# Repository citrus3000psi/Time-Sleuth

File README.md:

# Time Sleuth

A cheap and easy to build HDMI lag tester.  Through hole components were chosen to aid in assembly.  Resistors and Caps are still surface mount but a larger 0805 package size. 

An altera USB-Blaster is required to program the board. Firmware was created by Chriz2600 and can be found on his Github https://github.com/chriz2600/time-sleuth

For convenience the V1.1 PCB is shared on OSH Park.  Please order in 1.6mm thickness.
https://oshpark.com/shared_projects/Jw3gMtl8

A 3D printed case is also available but not required for the unit to function.  The STL file can be downloaded from here:
https://www.shapeways.com/product/DRHQ8MRWT/time-sleuth-top
https://www.shapeways.com/product/R2SNB5DNT/time-sleuth-bottom

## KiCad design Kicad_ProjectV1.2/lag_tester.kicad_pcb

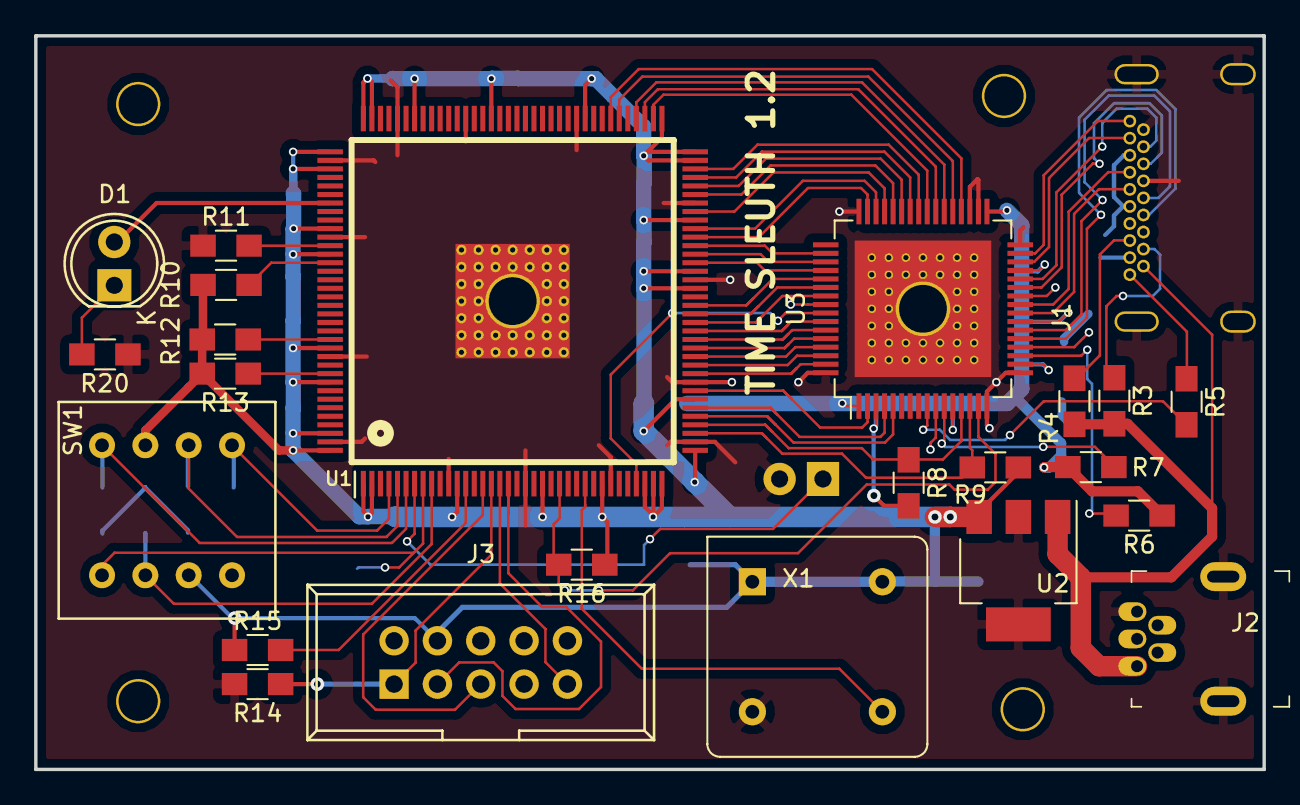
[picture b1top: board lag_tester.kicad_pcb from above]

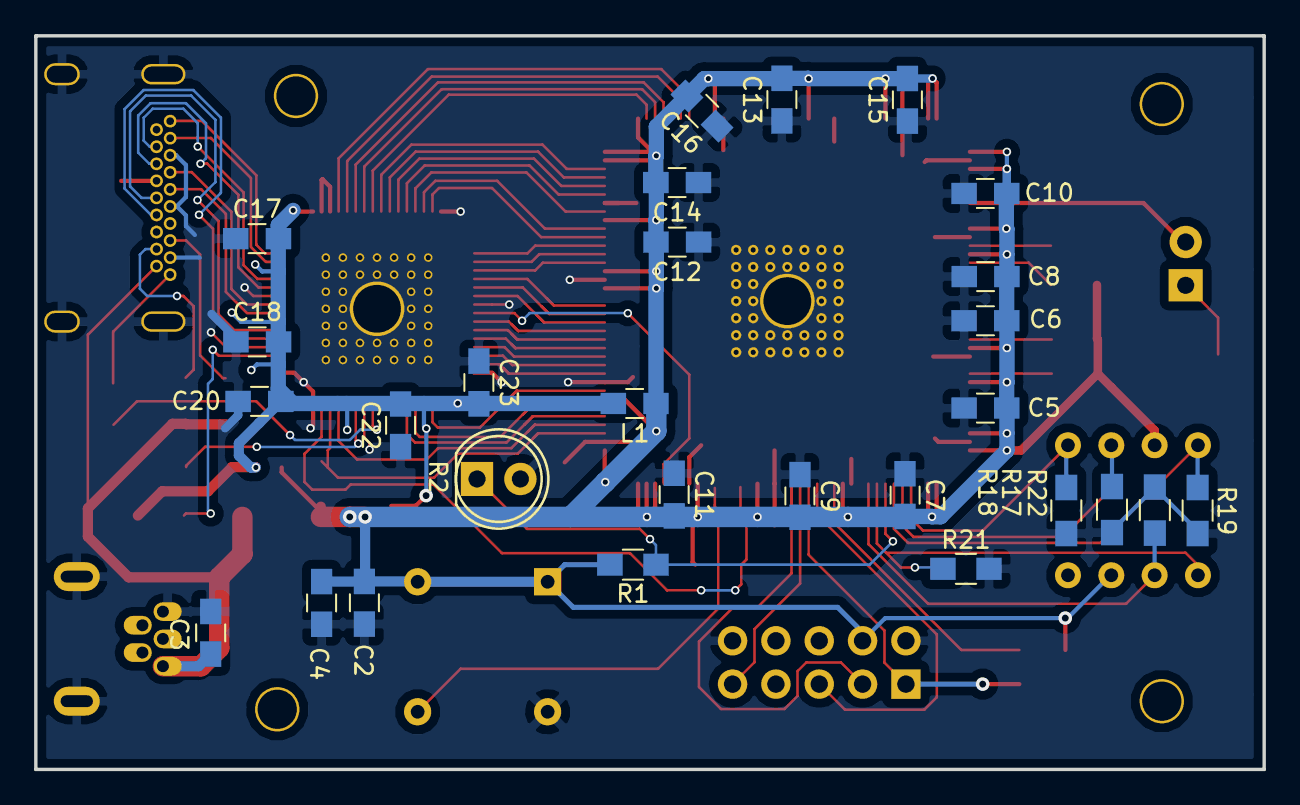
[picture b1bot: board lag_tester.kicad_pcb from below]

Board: 2 copper layers, 72.0 x 43.0 mm, 52 parts (28 on the bottom side), 67 nets.

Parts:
C2, C3, C23: 10u; C_0805_HandSoldering
C4, C5, C6, C7, C8, C9, C10, C11, C12, C13, C14, C15, C16, C17, C18, C20, C22: .1u; C_0805_HandSoldering
D1: LED; LED-5MM
J1: HDMI_A; HDMI_THRU
J2: USB_B_Mini; USB_Mini_B_Female_548190519
J3: AVR-JTAG-10; IDC_Header_Straight_10pins
L1: INDUCTOR; C_0805_HandSoldering
R1: 150; R_0805_HandSoldering
R2: R_PHOTO; LED-5MM
R3, R4, R10, R11, R12, R13, R14, R15, R17, R18, R19, R21, R22: 10K; R_0805_HandSoldering
R5: 1k; R_0805_HandSoldering
R6: 510; R_0805_HandSoldering
R7: 5K; R_0805_HandSoldering
R8, R9, R16: 2.2K; R_0805_HandSoldering
R20: 1K; R_0805_HandSoldering
SW1: SW_Coded; SS-10-23NP-LE
U1: 10M02SCE144I7G; altera144_wcenterpad
U2: TC1264-3.3VDBTR; SOT-223-3Lead_TabPin2
U3: TFP410PAP; TQFP-64_1EP_10x10mm_Pitch0.5mm
X1: CXO_DIP8; Oscillator_DIP-8

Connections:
/27CLK: U1.27, X1.5
/+3.3: C2.2, C4.2, C5.2, C6.2, C7.2, C8.2, C9.2, C10.2, C11.2, C12.2, C13.2, C14.2, C15.2, C16.2, J3.4, L1.1, R1.2, R9.1, R10.1, R12.1, R13.1, R15.1, R16.1, SW1.2, SW1.6, U1.1, U1.2, U1.12, U1.22, U1.29, U1.34, U1.35, U1.36, U1.37, U1.43, U1.56, U1.58, U1.64, U1.71, U1.72, U1.73, U1.82, U1.93, U1.102, U1.107, U1.108, U1.109, U1.111, U1.118, U1.121, U1.132, U1.136, U1.142, U1.144, U2.3, X1.1, X1.8
/+3.3_DVI: C17.2, C18.2, C20.2, C22.2, C23.2, L1.2, R6.1, R7.2, R8.2, U3.1, U3.3, U3.12, U3.18, U3.23, U3.29, U3.33
/+5: C3.2, J1.18, J2.5, R3.1, R4.1, U2.1
/+TMDS_0: J1.7, U3.25
/+TMDS_1: J1.4, U3.28
/+TMDS_2: J1.1, U3.31
/+TMDS_CLK: J1.10, U3.22
/-TMDS_0: J1.9, U3.24
/-TMDS_1: J1.6, U3.27
/-TMDS_2: J1.3, U3.30
/-TMDS_CLK: J1.12, U3.21
/A: R18.2, SW1.4, U1.4
/B: R17.1, SW1.3, U1.5
/C: R19.1, SW1.1, U1.6
/D: R21.1, SW1.8, U1.8
/D0: U1.46, U3.63
/D1: U1.47, U3.62
/D2: U1.48, U3.61
/D3: U1.49, U3.60
/D4: U1.50, U3.59
/D5: U1.51, U3.58
/D6: U1.52, U3.55
/D7: U1.53, U3.54
/D8: U1.54, U3.53
/D9: U1.59, U3.52
/D10: U1.60, U3.51
/D11: U1.61, U3.50
/D12: U1.62, U3.47
/D13: U1.63, U3.46
/D14: U1.65, U3.45
/D15: U1.67, U3.44
/D16: U1.68, U3.43
/D17: U1.69, U3.42
/D18: U1.70, U3.41
/D19: U1.74, U3.40
/D20: U1.75, U3.39
/D21: U1.76, U3.38
/D22: U1.78, U3.37
/D23: U1.79, U3.36
/DE: U1.44, U3.2
/DVI_CLK: U1.33, U3.57
/DVI_RST: R8.1, U1.40, U3.13
/E: R22.2, SW1.7, U1.9
/GND: C2.1, C3.1, C4.1, C5.1, C6.1, C7.1, C8.1, C9.1, C10.1, C11.1, C12.1, C13.1, C14.1, C15.1, C16.1, C17.1, C18.1, C20.1, C22.1, C23.1, J1.2, J1.5, J1.8, J1.11, J1.17, J1.SH, J2.1, J2.6, J3.2, J3.10, R2.2, R11.1, R14.2, R17.2, R18.1, R19.2, R20.1, R21.2, R22.1, U1.11, U1.20, U1.30, U1.38, U1.45, U1.57, U1.66, U1.83, U1.96, U1.104, U1.110, U1.119, U1.133, U1.143, U1.145, U2.2, U3.10, U3.16, U3.17, U3.20, U3.26, U3.32, U3.34, U3.35, U3.48, U3.56, U3.64, U3.65, X1.4
/HPD: J1.19, R5.1
/HSYNC: U1.42, U3.4
/SCL: R16.2, U1.24, U3.15
/SDA: R9.2, U1.39, U3.14
/SENSOR: R1.1, R2.1, U1.7
/TCK: J3.1, R14.1, U1.16
/TDI: J3.9, U1.17
/TDO: J3.3, U1.18
/TMS: J3.5, U1.15
/VSYNC: U1.41, U3.5
unnamed: D1.1, R20.2
unnamed: D1.2, U1.115
unnamed: J1.15, R4.2
unnamed: J1.16, R3.2
unnamed: R5.2, U3.9
unnamed: R6.2, U3.19
unnamed: R7.1, U3.11
unnamed: R10.2, U1.122
unnamed: R11.2, U1.120
unnamed: R12.2, U1.131
unnamed: R13.2, U1.135
unnamed: R15.2, U1.13

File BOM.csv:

Reference, Quantity, Value, Footprint,Notes,DigiKey #
C2 C3 C23,2,10u,Capacitors_SMD:C_0805_HandSoldering,16V,
C10 C11 C12 C13 C14 C15 C16 C17 C18 C20 C22 C4 C5 C6 C7 C8 C9 ,18,.1u,Capacitors_SMD:C_0805_HandSoldering,50V,
D1 ,1,LED,LEDs:LED-5MM,,
J1 ,1,2000-1-1-20-00-BK,pads:HDMI_THRU,,1175-1700-ND 
J2 ,1,548190519,digikey-footprints:USB_Mini_B_Female_548190519,,WM17115-ND 
J3 ,1,AVR-JTAG-10,Connect:IDC_Header_Straight_10pins,,ED1543-ND 
L1 ,1,MH2029-100Y,Capacitors_SMD:C_0805_HandSoldering,10 Ohm,MH2029-100YCT-ND
R1 ,1,300K,Resistors_SMD:R_0805_HandSoldering,,
R16 R8 R9 ,3,2.2K,Resistors_SMD:R_0805_HandSoldering,,
R2 ,1,R_PHOTO,LEDs:LED-5MM,,475-1437-ND 
R20 ,1,1K,Resistors_SMD:R_0805_HandSoldering,,
R10 R11 R12 R13 R14 R15 R17 R18 R19 R3 R4 ,11,10K,Resistors_SMD:R_0805_HandSoldering,,
R5 ,1,1k,Resistors_SMD:R_0805_HandSoldering,,
R6 ,1,510,Resistors_SMD:R_0805_HandSoldering,,
R7 ,1,5K,Resistors_SMD:R_0805_HandSoldering,,
SW1 ,1,SS-10-23NP-LE,pads:SS-10-23NP-LE,,563-1084-ND
SW1_OPT ,1,SS-10-15SP-LE,pads:SS-10-23NP-LE,,563-1078-ND
U1 ,1,10M02SCE144C8G,Altera:altera144_wcenterpad,,544-3098-ND 
U2 ,1,TC1264-3.3VDBTR,TO_SOT_Packages_SMD:SOT-223-3Lead_TabPin2,,TC1264-3.3VDBCT-ND 
U3 ,1,TFP410PAP,Housings_QFP:TQFP-64_1EP_10x10mm_Pitch0.5mm,,296-12666-ND 
X1 ,1,CXO_DIP8,Oscillators:Oscillator_DIP-8,27Mhz,535-9194-5-ND

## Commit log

2019-01-31 Add Project Files
2019-01-31 Create LICENSE
2020-08-07 Added 5 Position Switch
2020-08-07 Add V1.2 which has 5 position switch.
2021-03-12 Fix up BOM
    * Correct capacitor quantities; there's one more 10uF and one fewer
    0.1uF
    * Fold both separate 1K resistors into one line item
    * Add the missing R21 and R22 resistors and update the quantity
